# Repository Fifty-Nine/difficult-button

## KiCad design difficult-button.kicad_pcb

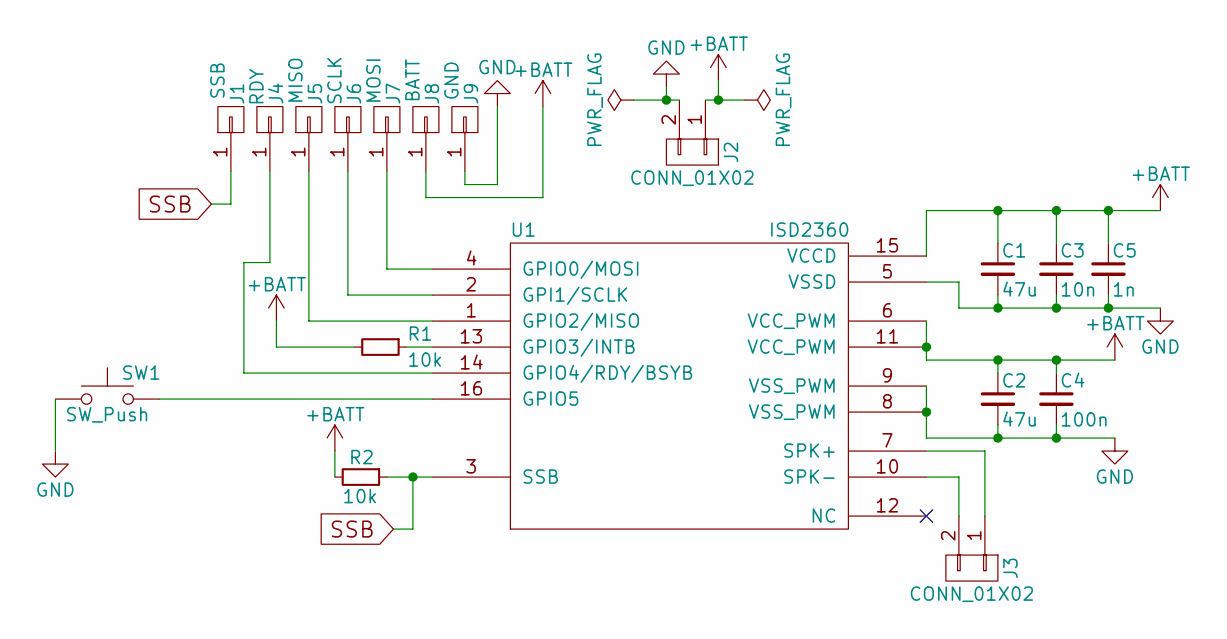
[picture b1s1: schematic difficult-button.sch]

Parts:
C1, C2: 47u; C_0603_HandSoldering
C3: 10n; C_0603_HandSoldering
C4: 100n; C_0603_HandSoldering
C5: 1n; C_0603_HandSoldering
J1: SSB; Measurement_Point_Square-SMD-Pad_Big
J2, J3: CONN_01X02; Pin_Header_Straight_1x02_Pitch2.54mm
J4: RDY; Measurement_Point_Square-SMD-Pad_Big
J5: MISO; Measurement_Point_Square-SMD-Pad_Big
J6: SCLK; Measurement_Point_Square-SMD-Pad_Big
J7: MOSI; Measurement_Point_Square-SMD-Pad_Big
J8: BATT; Measurement_Point_Square-SMD-Pad_Big
J9: GND; Measurement_Point_Square-SMD-Pad_Big
R1, R2: 10k; R_0603_HandSoldering
SW1: SW_Push; DOME_BTN
U1: ISD2360; SOIC-16W_7.5x10.3mm_Pitch1.27mm

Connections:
+BATT: C1.1, C2.1, C3.1, C4.1, C5.1, J2.1, J8.1, R1.2, R2.2, U1.6 (VCC_PWM), U1.11 (VCC_PWM), U1.15 (VCCD)
GND: C1.2, C2.2, C3.2, C4.2, C5.2, J2.2, J9.1, SW1.1, U1.5 (VSSD), U1.8 (VSS_PWM), U1.9 (VSS_PWM)
unnamed: J3.1, U1.7 (SPK+)
unnamed: J3.2, U1.10 (SPK-)
unnamed: J4.1, U1.14 (GPIO4/RDY/BSYB)
unnamed: J5.1, U1.1 (GPIO2/MISO)
unnamed: J6.1, U1.2 (GPI1/SCLK)
unnamed: J7.1, U1.4 (GPIO0/MOSI)
unnamed: R1.1, U1.13 (GPIO3/INTB)
unnamed: SW1.2, U1.16 (GPIO5)
SSB: J1.1, R2.1, U1.3 (SSB)

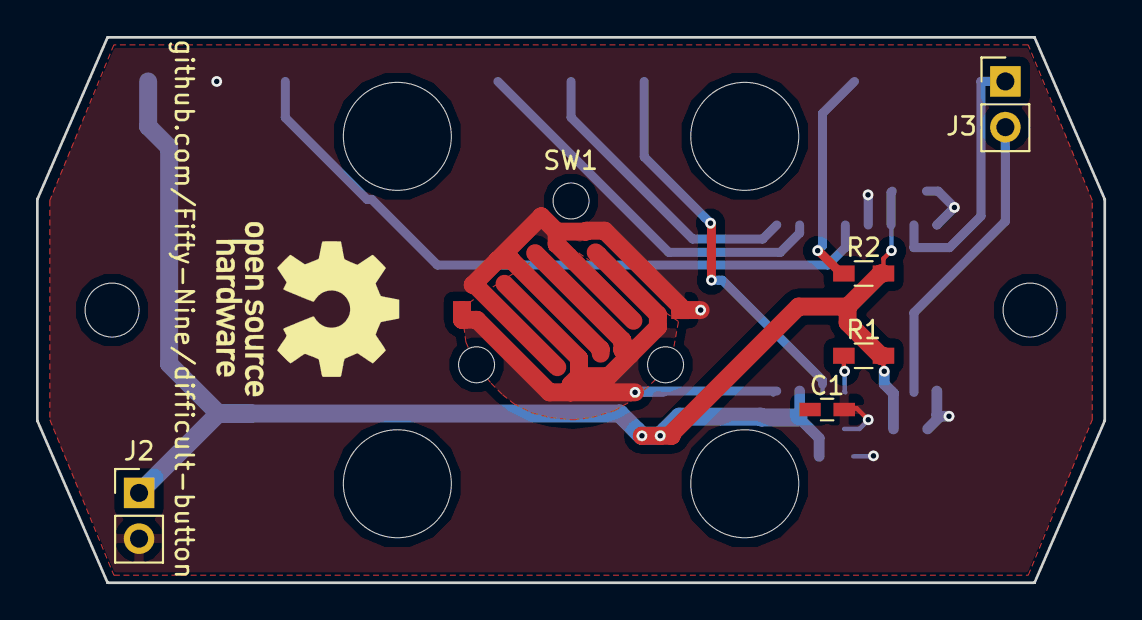
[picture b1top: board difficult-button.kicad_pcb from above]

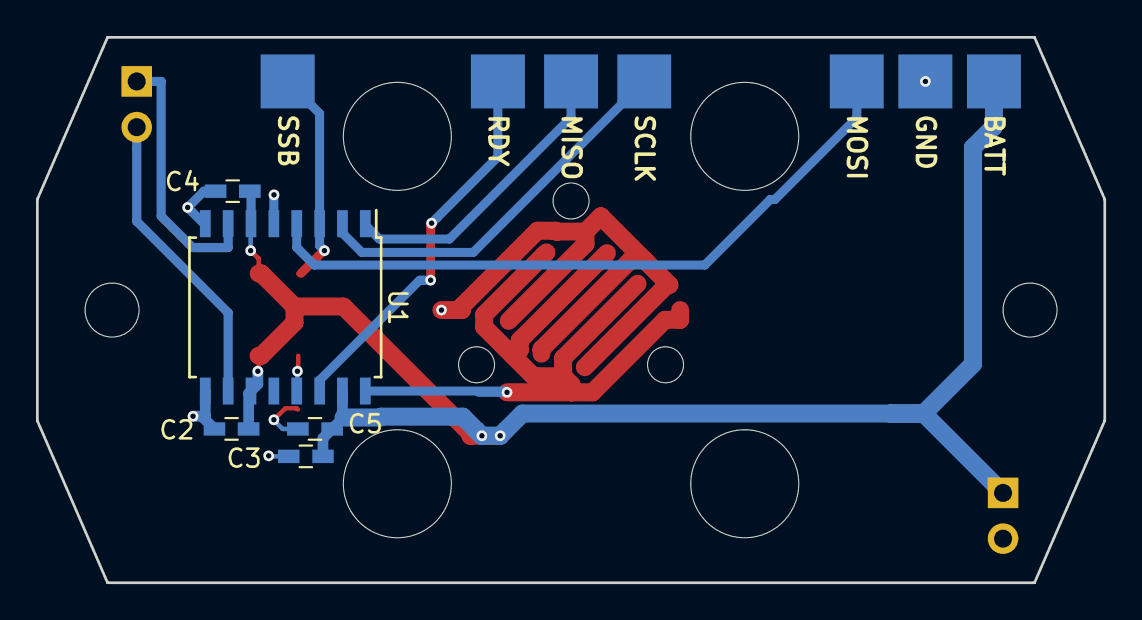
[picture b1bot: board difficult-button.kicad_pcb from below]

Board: 2 copper layers, 59.3 x 30.3 mm, 18 parts (12 on the bottom side), 11 nets.

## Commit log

2017-08-03 Initial revision.
2017-08-03 Disable extended gerbers for Seeedstudio.
